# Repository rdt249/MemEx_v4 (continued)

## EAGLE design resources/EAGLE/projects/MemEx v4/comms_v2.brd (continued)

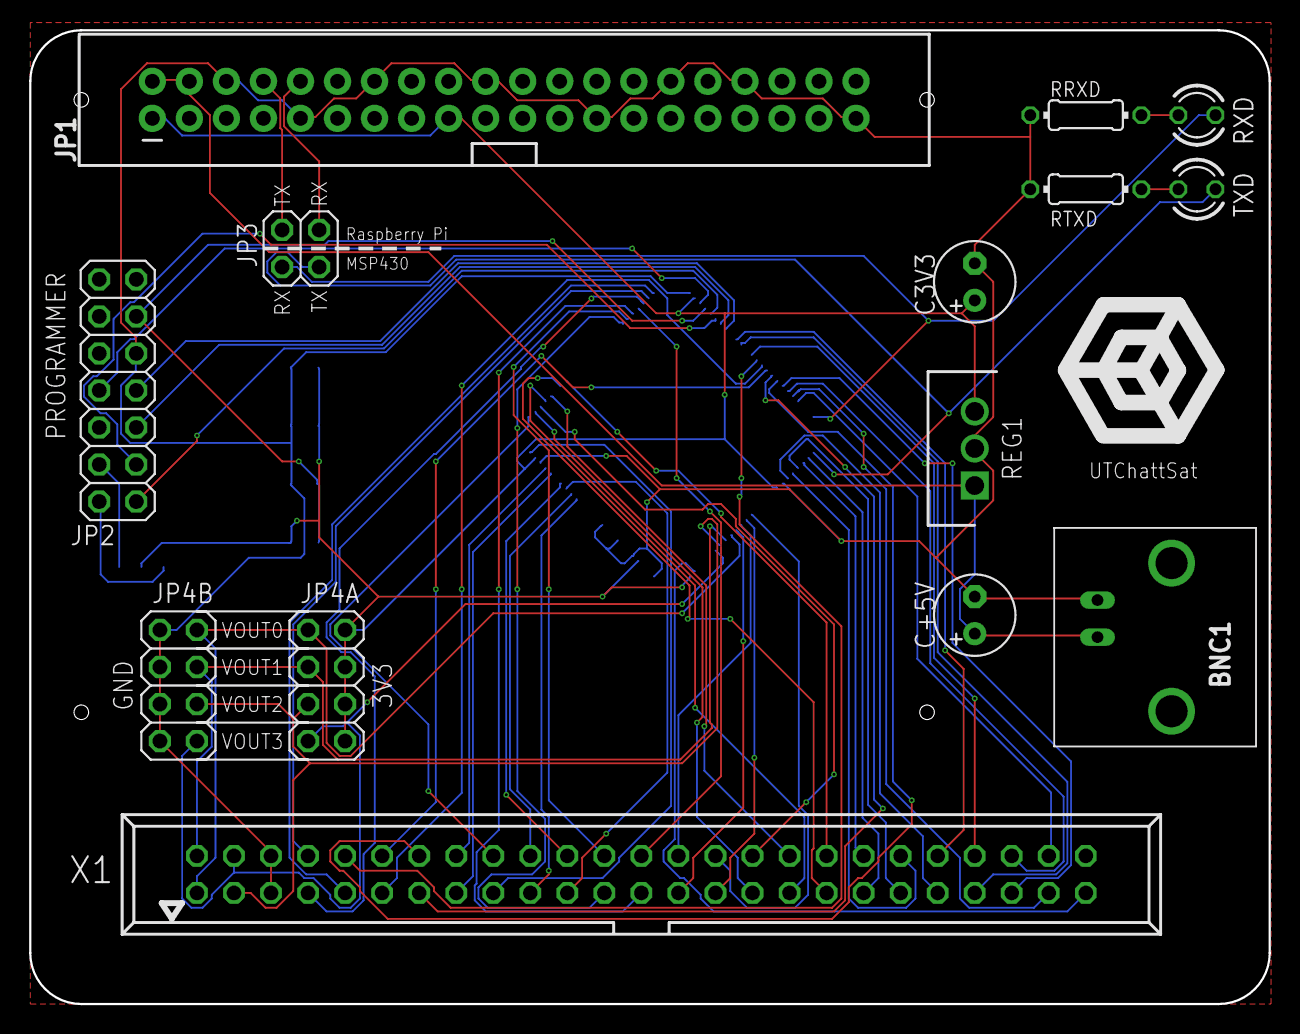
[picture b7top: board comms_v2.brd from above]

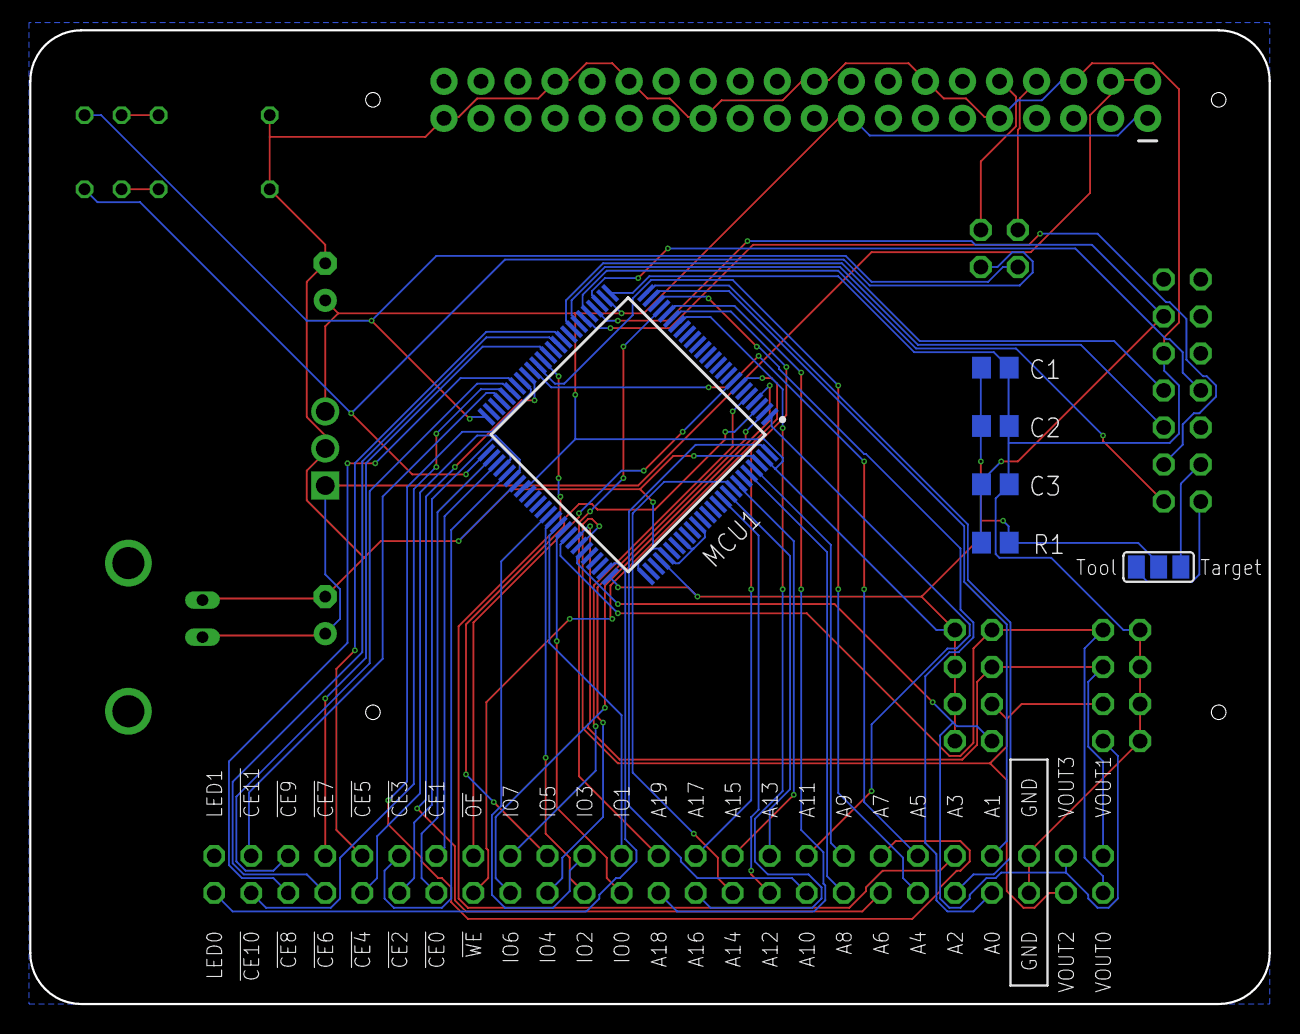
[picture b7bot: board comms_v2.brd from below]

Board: 2 copper layers, 85.0 x 66.8 mm, 20 parts (6 on the bottom side), 64 nets.

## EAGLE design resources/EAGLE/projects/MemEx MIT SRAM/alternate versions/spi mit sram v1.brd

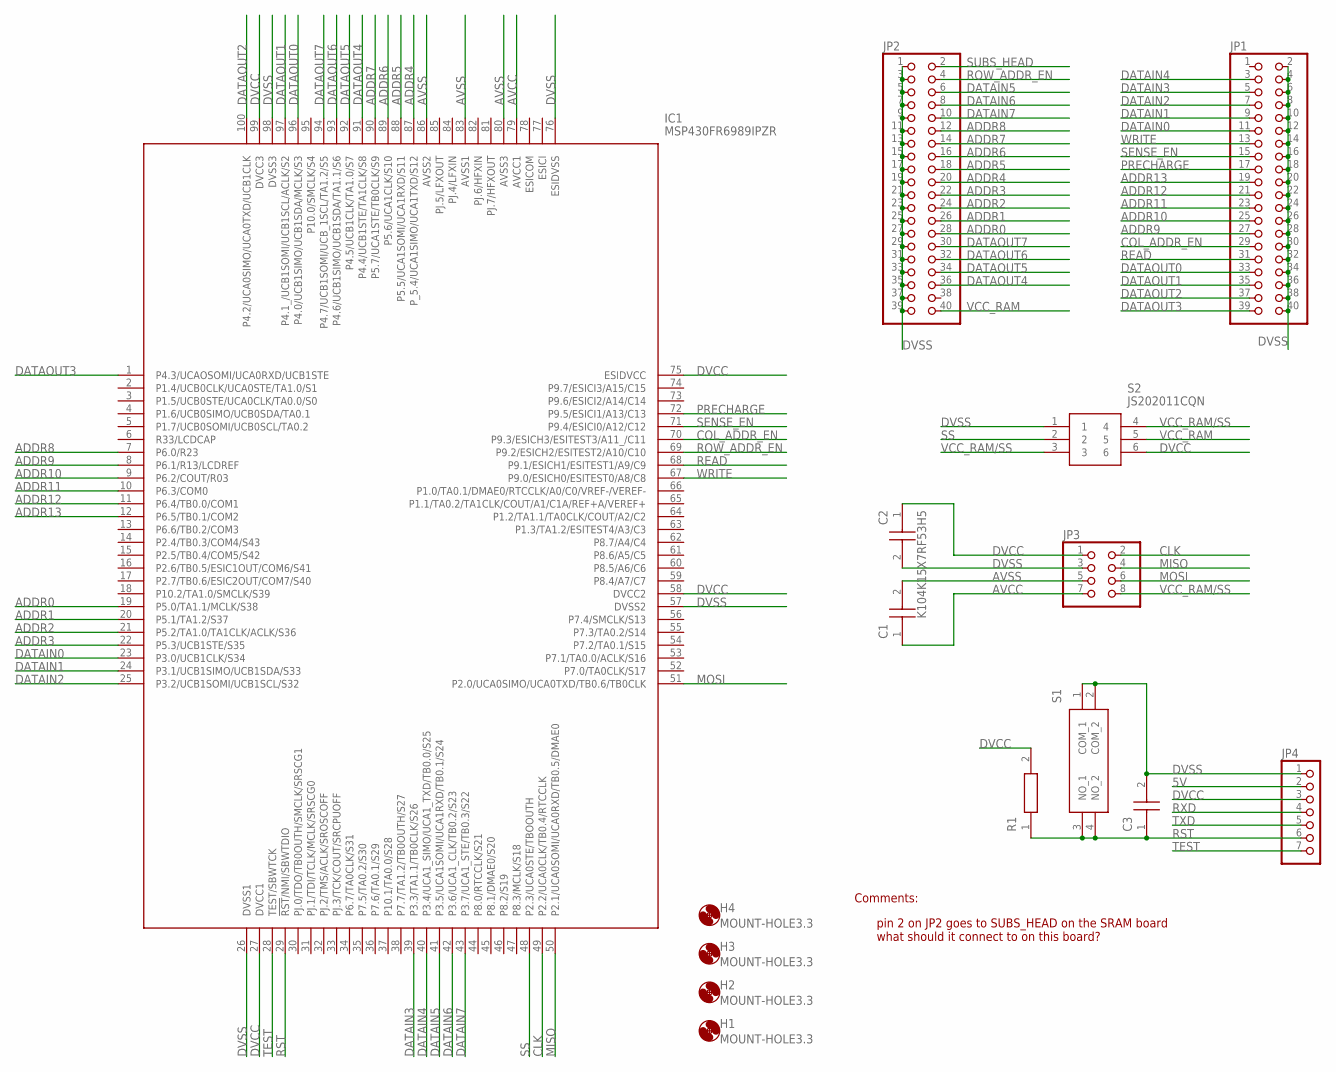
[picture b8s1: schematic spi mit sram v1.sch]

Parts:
C1, C2, C3: K104K15X7RF53H5
H1, H2, H3, H4: MOUNT-HOLE3.3; 3,3
IC1: MSP430FR6989IPZR; QFP50P1600X1600X160-100N
JP1, JP2: PINHD-2X20; 2X20
JP3: PINHD-2X4; 2X04
JP4: PINHD-1X7; 1X07
R1: MF0207FTE52-10K; RESAD1590W60L630D240
S1: 1825910-3; 18259103
S2: JS202011CQN

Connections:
5V: JP4.2
ADDR0: IC1.19 (P5.0/TA1.1/MCLK/S38), JP2.28
ADDR1: IC1.20 (P5.1/TA1.2/S37), JP2.26
ADDR2: IC1.21 (P5.2/TA1.0/TA1CLK/ACLK/S36), JP2.24
ADDR3: IC1.22 (P5.3/UCB1STE/S35), JP2.22
ADDR4: IC1.87 (P_5.4/UCA1SIMO/UCA1TXD/S12), JP2.20
ADDR5: IC1.88 (P5.5/UCA1SOMI/UCA1RXD/S11), JP2.18
ADDR6: IC1.89 (P5.6/UCA1CLK/S10), JP2.16
ADDR7: IC1.90 (P5.7/UCA1STE/TB0CLK/S9), JP2.14
ADDR8: IC1.7 (P6.0/R23), JP2.12
ADDR9: IC1.8 (P6.1/R13/LCDREF), JP1.27
ADDR10: IC1.9 (P6.2/COUT/R03), JP1.25
ADDR11: IC1.10 (P6.3/COM0), JP1.23
ADDR12: IC1.11 (P6.4/TB0.0/COM1), JP1.21
ADDR13: IC1.12 (P6.5/TB0.1/COM2), JP1.19
AVCC: C1.1, IC1.79 (AVCC1), JP3.7
AVSS: C1.2, IC1.80 (AVSS3), IC1.83 (AVSS1), IC1.86 (AVSS2), JP3.5
CLK: IC1.49 (P2.2/UCA0CLK/TB0.4/RTCCLK), JP3.2
COL_ADDR_EN: IC1.70 (P9.3/ESICH3/ESITEST3/A11_/C11), JP1.29
DATAIN0: IC1.23 (P3.0/UCB1CLK/S34), JP1.11
DATAIN1: IC1.24 (P3.1/UCB1SIMO/UCB1SDA/S33), JP1.9
DATAIN2: IC1.25 (P3.2/UCB1SOMI/UCB1SCL/S32), JP1.7
DATAIN3: IC1.39 (P3.3/TA1.1/TB0CLK/S26), JP1.5
DATAIN4: IC1.40 (P3.4/UCA1_SIMO/UCA1_TXD/TB0.0/S25), JP1.3
DATAIN5: IC1.41 (P3.5/UCA1SOMI/UCA1RXD/TB0.1/S24), JP2.6
DATAIN6: IC1.42 (P3.6/UCA1_CLK/TB0.2/S23), JP2.8
DATAIN7: IC1.43 (P3.7/UCA1_STE/TB0.3/S22), JP2.10
DATAOUT0: IC1.96 (P4.0/UCB1SIMO/UCB1SDA/MCLK/S3), JP1.33
DATAOUT1: IC1.97 (P4.1_/UCB1SOMI/UCB1SCL/ACLK/S2), JP1.35
DATAOUT2: IC1.100 (P4.2/UCA0SIMO/UCA0TXD/UCB1CLK), JP1.37
DATAOUT3: IC1.1 (P4.3/UCAOSOMI/UCA0RXD/UCB1STE), JP1.39
DATAOUT4: IC1.91 (P4.4/UCB1STE/TA1CLK/S8), JP2.36
DATAOUT5: IC1.92 (P4.5/UCB1CLK/TA1.0/S7), JP2.34
DATAOUT6: IC1.93 (P4.6/UCB1SIMO/UCB1SDA/TA1.1/S6), JP2.32
DATAOUT7: IC1.94 (P4.7/UCB1SOMI/UCB_1SCL/TA1.2/S5), JP2.30
DVCC: C2.1, IC1.27 (DVCC1), IC1.58 (DVCC2), IC1.75 (ESIDVCC), IC1.99 (DVCC3), JP3.1, JP4.3, R1.2, S2.6
DVSS: C2.2, C3.2, IC1.26 (DVSS1), IC1.57 (DVSS2), IC1.76 (ESIDVSS), IC1.98 (DVSS3), JP1.2, JP1.4, JP1.6, JP1.8, JP1.10, JP1.12, JP1.14, JP1.16, JP1.18, JP1.20, JP1.22, JP1.24, JP1.26, JP1.28, JP1.30, JP1.32, JP1.34, JP1.36, JP1.38, JP1.40, JP2.1, JP2.3, JP2.5, JP2.7, JP2.9, JP2.11, JP2.13, JP2.15, JP2.17, JP2.19, JP2.21, JP2.23, JP2.25, JP2.27, JP2.29, JP2.31, JP2.33, JP2.35, JP2.37, JP2.39, JP3.3, JP4.1, S1.1 (COM_1), S1.2 (COM_2), S2.1
MISO: IC1.50 (P2.1/UCA0SOMI/UCA0RXD/TB0.5/DMAE0), JP3.4
MOSI: IC1.51 (P2.0/UCA0SIMO/UCA0TXD/TB0.6/TB0CLK), JP3.6
PRECHARGE: IC1.72 (P9.5/ESICI1/A13/C13), JP1.17
READ: IC1.68 (P9.1/ESICH1/ESITEST1/A9/C9), JP1.31
ROW_ADDR_EN: IC1.69 (P9.2/ESICH2/ESITEST2/A10/C10), JP2.4
RST: C3.1, IC1.29 (!RST!/NMI/SBWTDIO), JP4.6, R1.1, S1.3 (NO_1), S1.4 (NO_2)
RXD: JP4.4
SENSE_EN: IC1.71 (P9.4/ESICI0/A12/C12), JP1.15
SS: IC1.48 (P2.3/UCA0STE/TBOOUTH), S2.2
SUBS_HEAD: JP2.2
TEST: IC1.28 (TEST/SBWTCK), JP4.7
TXD: JP4.5
VCC_RAM: JP2.40, S2.5
VCC_RAM/SS: JP3.8, S2.3, S2.4
WRITE: IC1.67 (P9.0/ESICH0/ESITEST0/A8/C8), JP1.13

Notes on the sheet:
Comments:
pin 2 on JP2 goes to SUBS_HEAD on the SRAM board what should it connect to on this board?

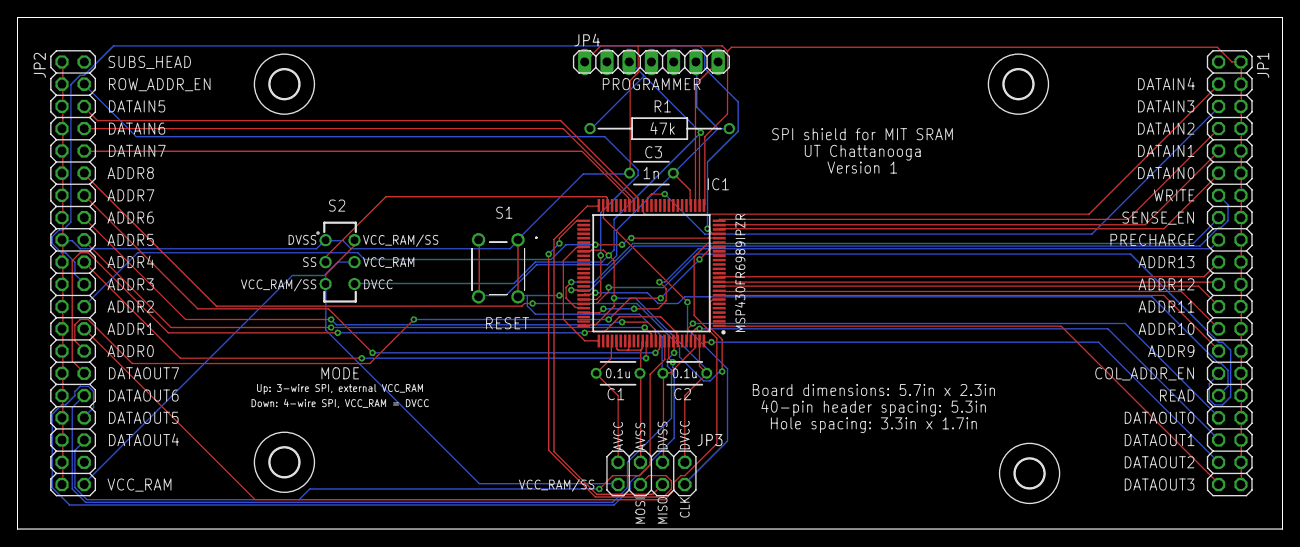
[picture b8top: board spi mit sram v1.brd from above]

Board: 2 copper layers, 144.4 x 58.4 mm, 15 parts (0 on the bottom side), 48 nets.

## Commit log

2021-11-11 comm controller done
2021-11-11 added CCS and EAGLE resources
